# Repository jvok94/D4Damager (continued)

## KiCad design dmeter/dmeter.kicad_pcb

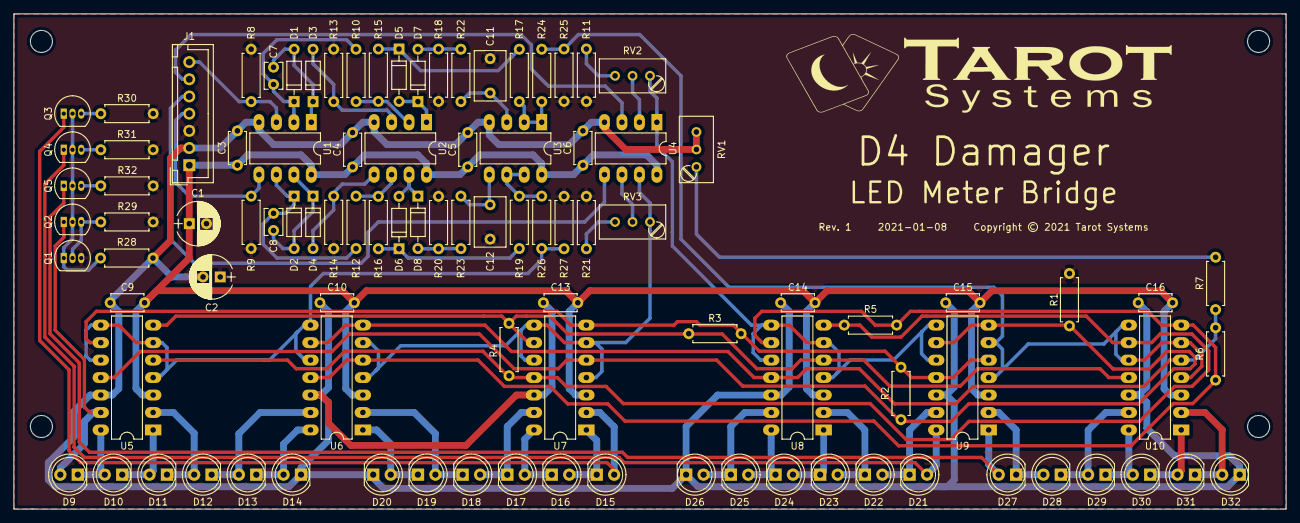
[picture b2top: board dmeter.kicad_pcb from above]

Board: 2 copper layers, 185.0 x 72.0 mm, 104 parts (0 on the bottom side), 69 nets.

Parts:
C1, C2: 100u 25V; CP_Radial_D6.3mm_P2.50mm
C3, C4, C5, C6, C9, C10, C13, C14, C15, C16: 100n; C_Disc_D4.7mm_W2.5mm_P5.00mm
C7, C8: 33p; C_Disc_D3.8mm_W2.6mm_P2.50mm
C11, C12: 560n; C_Rect_L7.2mm_W4.5mm_P5.00mm_FKS2_FKP2_MKS2_MKP2
D1, D2, D3, D4, D5, D6, D7, D8: 1N4148; D_DO-35_SOD27_P7.62mm_Horizontal
D9, D10, D11, D12, D15, D16, D17, D18, D19, D20, D21, D22, D23, D24, D25, D26, D27, D28, D29, D30: GREEN; LED_D5.0mm
D13, D31: YELLOW; LED_D5.0mm
D14, D32: RED; LED_D5.0mm
G1: LOGO; tarot_logo_fsilk_60mm
H1, H2, H3, H4: M3; MountingHole_3.2mm_M3
J1: INPUT; JST_XH_B07B-XH-A_07x2.50mm_Straight
Q1, Q2, Q3, Q4, Q5: BC556; TO-92_Inline_Narrow_Oval
R1, R2: 1k; R_Axial_DIN0207_L6.3mm_D2.5mm_P7.62mm_Horizontal_FabText
R3: 2k; R_Axial_DIN0207_L6.3mm_D2.5mm_P7.62mm_Horizontal_FabText
R4: 3k9; R_Axial_DIN0207_L6.3mm_D2.5mm_P7.62mm_Horizontal_FabText
R5: 8k2; R_Axial_DIN0207_L6.3mm_D2.5mm_P7.62mm_Horizontal_FabText
R6: 16k; R_Axial_DIN0207_L6.3mm_D2.5mm_P7.62mm_Horizontal_FabText
R7: 240k; R_Axial_DIN0207_L6.3mm_D2.5mm_P7.62mm_Horizontal_FabText
R8, R9, R10, R12, R13, R14, R15, R16, R17, R19, R24, R25, R27: 10k; R_Axial_DIN0207_L6.3mm_D2.5mm_P7.62mm_Horizontal_FabText
R11, R21: 390; R_Axial_DIN0207_L6.3mm_D2.5mm_P7.62mm_Horizontal_FabText
R18, R20: 1M; R_Axial_DIN0207_L6.3mm_D2.5mm_P7.62mm_Horizontal_FabText
R22, R23, R28: 5k6; R_Axial_DIN0207_L6.3mm_D2.5mm_P7.62mm_Horizontal_FabText
R26: 30k; R_Axial_DIN0207_L6.3mm_D2.5mm_P7.62mm_Horizontal_FabText
R29, R30, R31, R32: 100; R_Axial_DIN0207_L6.3mm_D2.5mm_P7.62mm_Horizontal_FabText
RV1, RV2, RV3: 10k; Potentiometer_Trimmer_Bourns_3296W_FabText
U1, U2, U3, U4: TL072; DIP-8_W7.62mm_LongPads
U5, U6, U7, U8, U9, U10: LM339; DIP-14_W7.62mm_LongPads

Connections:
+15V: C1.1, C3.1, C4.1, C5.1, C6.1, C9.1, C10.1, C13.1, C14.1, C15.1, C16.1, J1.1, U1.8 (V+), U2.8 (V+), U3.8 (V+), U4.8 (V+), U5.3 (V+), U6.3 (V+), U7.3 (V+), U8.3 (V+), U9.3 (V+), U10.3 (V+)
-15V: C2.2, C3.2, C4.2, C5.2, C6.2, C9.2, C10.2, C13.2, C14.2, C15.2, C16.2, D14.1 (K), D20.1 (K), D26.1 (K), D32.1 (K), J1.2, R28.2, RV1.2, RV1.3, U1.4 (V-), U2.4 (V-), U3.4 (V-), U4.4 (V-), U5.12 (V-), U6.12 (V-), U7.12 (V-), U8.12 (V-), U9.12 (V-), U10.12 (V-)
/VU0: R6.2, R7.1, U6.7 (+), U6.9 (+), U8.11 (+), U10.5 (+)
/VU6: R5.2, R6.1, U6.5 (+), U6.11 (+), U8.9 (+), U10.7 (+)
/VU12: R4.2, R5.1, U5.5 (+), U7.11 (+), U8.7 (+), U10.9 (+)
/VU18: R3.2, R4.1, U5.7 (+), U7.9 (+), U8.5 (+), U10.11 (+)
/VU24: R2.2, R3.1, U5.9 (+), U7.7 (+), U9.5 (+), U9.11 (+)
/VU30: R1.2, R2.1, U5.11 (+), U7.5 (+), U9.7 (+), U9.9 (+)
GND: C1.2, C2.1, C11.2, C12.2, J1.3, Q1.3 (E), R1.1, R8.2, R9.2, R11.2, R13.2, R14.2, R18.2, R20.2, R21.2, R25.2, R27.2, R29.1, R30.1, R31.1, R32.1
unnamed: C7.1, D1.1 (K), R10.2, U1.2 (-)
unnamed: C7.2, D1.2 (A), D3.1 (K), U1.1
unnamed: C8.1, D2.1 (K), R12.2, U1.6 (-)
unnamed: C8.2, D2.2 (A), D4.1 (K), U1.7
unnamed: C11.1, R22.1, U3.3 (+)
unnamed: C12.1, R23.1, U3.5 (+)
unnamed: D3.2 (A), R13.1, U2.3 (+)
unnamed: D4.2 (A), R14.1, U2.5 (+)
unnamed: D5.1 (K), R15.1, R17.2
unnamed: D5.2 (A), D7.1 (K), U2.1
unnamed: D6.1 (K), R16.1, R19.2
unnamed: D6.2 (A), D8.1 (K), U2.7
unnamed: D7.2 (A), R18.1, R22.2
unnamed: D8.2 (A), R20.1, R23.2
unnamed: D9.2 (A), Q2.1 (C), U5.13
unnamed: D10.1 (K), D11.2 (A), U5.1
unnamed: D9.1 (K), D10.2 (A), U5.14
unnamed: D11.1 (K), D12.2 (A), U5.2
unnamed: D12.1 (K), D13.2 (A), U6.13
unnamed: D13.1 (K), D14.2 (A), U6.14
unnamed: D15.1 (K), D16.2 (A), U7.1
unnamed: D15.2 (A), Q3.1 (C), U7.2
unnamed: D16.1 (K), D17.2 (A), U7.14
unnamed: D17.1 (K), D18.2 (A), U7.13
unnamed: D18.1 (K), D19.2 (A), U6.2
unnamed: D19.1 (K), D20.2 (A), U6.1
unnamed: D21.1 (K), D22.2 (A), U9.13
unnamed: D21.2 (A), Q4.1 (C), U9.14
unnamed: D22.1 (K), D23.2 (A), U8.2
unnamed: D23.1 (K), D24.2 (A), U8.1
unnamed: D24.1 (K), D25.2 (A), U8.14
unnamed: D25.1 (K), D26.2 (A), U8.13
unnamed: D27.1 (K), D28.2 (A), U9.2
unnamed: D27.2 (A), Q5.1 (C), U9.1
unnamed: D28.1 (K), D29.2 (A), U10.13
unnamed: D29.1 (K), D30.2 (A), U10.14
unnamed: D30.1 (K), D31.2 (A), U10.1
unnamed: D31.1 (K), D32.2 (A), U10.2
unnamed: J1.4, R9.1, U1.5 (+)
unnamed: J1.5, U4.5 (+)
unnamed: J1.6, U4.3 (+)
unnamed: J1.7, R8.1, U1.3 (+)
unnamed: Q1.1 (C), Q2.2 (B), Q3.2 (B), Q4.2 (B), Q5.2 (B), R28.1
unnamed: Q1.2 (B), Q2.3 (E), R29.2
unnamed: Q3.3 (E), R30.2
unnamed: Q4.3 (E), R31.2
unnamed: Q5.3 (E), R32.2
unnamed: R7.2, RV1.1
unnamed: R10.1, R15.2, U2.2 (-)
unnamed: R11.1, RV2.3
unnamed: R12.1, R16.2, U2.6 (-)
unnamed: R17.1, R24.1, U3.1, U3.2 (-)
unnamed: R19.1, R26.1, U3.6 (-), U3.7
unnamed: R21.1, RV3.3
unnamed: R24.2, R25.1, U9.4 (-), U9.6 (-), U10.4 (-), U10.6 (-), U10.8 (-), U10.10 (-)
unnamed: R26.2, R27.1, U5.4 (-), U5.6 (-), U5.8 (-), U5.10 (-), U6.8 (-), U6.10 (-)
unnamed: RV2.1, U4.1, U8.4 (-), U8.6 (-), U8.8 (-), U8.10 (-), U9.8 (-), U9.10 (-)
unnamed: RV2.2, U4.2 (-)
unnamed: RV3.1, U4.7, U6.4 (-), U6.6 (-), U7.4 (-), U7.6 (-), U7.8 (-), U7.10 (-)
unnamed: RV3.2, U4.6 (-)

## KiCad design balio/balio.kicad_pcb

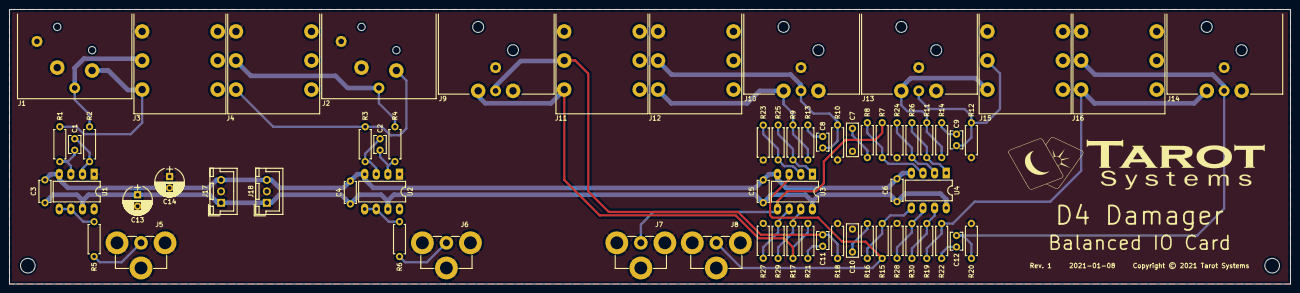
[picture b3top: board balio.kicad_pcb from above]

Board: 2 copper layers, 280.0 x 60.0 mm, 69 parts (0 on the bottom side), 41 nets.

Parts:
C1, C2, C8, C9, C11, C12: 560p; C_Disc_D3.8mm_W2.6mm_P2.50mm
C3, C4, C5, C6: 100n; C_Disc_D4.7mm_W2.5mm_P5.00mm
C7, C10: *; C_Rect_L7.2mm_W2.5mm_P5.00mm_FKS2_FKP2_MKS2_MKP2
C13, C14: 100u 25V; CP_Radial_D6.3mm_P2.50mm
G1: LOGO; tarot_logo_fsilk_60mm
H1, H2: M3; MountingHole_3.2mm_M3
J1: IN1; NC3FAAH2
J2: IN2; NC3FAAH2
J3: IN1; CL12345
J4: IN2; CL12345
J5: OUT1; NYS354
J6: OUT2; NYS354
J7: IN3; NYS354
J8: IN4; NYS354
J9: OUT3; NC3MAAH
J10: OUT4; NC3MAAH
J11: OUT3; CL12345
J12: OUT4; CL12345
J13: MON3; NC3MAAH
J14: MON4; NC3MAAH
J15: MON3; CL12345
J16: MON4; CL12345
J17, J18: POWER; JST_XH_B03B-XH-A_03x2.50mm_Straight
R1, R2, R3, R4, R23, R24, R25, R26, R27, R28, R29, R30: 2k2; R_Axial_DIN0207_L6.3mm_D2.5mm_P7.62mm_Horizontal_FabText
R5, R6, R9, R10, R11, R12, R13, R14, R17, R18, R19, R20, R21, R22: 220; R_Axial_DIN0207_L6.3mm_D2.5mm_P7.62mm_Horizontal_FabText
R7, R8, R15, R16: *; R_Axial_DIN0207_L6.3mm_D2.5mm_P7.62mm_Horizontal_FabText
U1, U2: INA134; DIP-8_W7.62mm_LongPads
U3, U4: TL072; DIP-8_W7.62mm_LongPads

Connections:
+15V: C3.2, C4.2, C5.1, C6.1, C13.1, J17.1, J18.1, U1.7 (VDD), U2.7 (VDD), U3.8 (V+), U4.8 (V+)
-15V: C3.1, C4.1, C5.2, C6.2, C14.2, J17.3, J18.3, U1.4 (VSS), U2.4 (VSS), U3.4 (V-), U4.4 (V-)
GND: C7.2, C10.2, C13.2, C14.1, J1.1, J1.G, J2.1, J2.G, J3.S, J4.S, J5.2 (Ext), J6.2 (Ext), J7.2 (Ext), J8.2 (Ext), J9.1, J9.G, J10.1, J10.G, J11.S, J12.S, J13.1, J13.G, J14.1, J14.G, J15.S, J16.S, J17.2, J18.2, R10.2, R12.2, R18.2, R20.2, R23.1, R24.1, R27.1, R28.1, U1.1 (REF), U2.1 (REF)
unnamed: C1.1, R2.1, U1.2 (IN-)
unnamed: C1.2, R1.1, U1.3 (IN+)
unnamed: C2.1, R4.1, U2.2 (IN-)
unnamed: C2.2, R3.1, U2.3 (IN+)
unnamed: C7.1, R8.2
unnamed: C8.1, R13.1
unnamed: C8.2, J10.3, J12.R, R10.1
unnamed: C9.1, R14.1
unnamed: C9.2, J13.3, J15.R, R12.1
unnamed: C10.1, R16.2
unnamed: C11.1, R21.1
unnamed: C11.2, J9.3, J11.R, R18.1
unnamed: C12.1, R22.1
unnamed: C12.2, J14.3, J16.R, R20.1
unnamed: J1.2, J3.T, R1.2
unnamed: J1.3, J3.R, R2.2
unnamed: J2.2, J4.T, R3.2
unnamed: J2.3, J4.R, R4.2
unnamed: J5.1 (In), R5.1
unnamed: J6.1 (In), R6.1
unnamed: J7.1 (In), R7.1, U3.5 (+)
unnamed: J8.1 (In), R15.1, U3.3 (+)
unnamed: J10.2, J12.T, R9.1, R13.2
unnamed: J9.2, J11.T, R17.1, R21.2
unnamed: J13.2, J15.T, R11.1, R14.2
unnamed: J14.2, J16.T, R19.1, R22.2
unnamed: R5.2, U1.5 (SENSE), U1.6 (OUT)
unnamed: R6.2, U2.5 (SENSE), U2.6 (OUT)
unnamed: R7.2, R8.1, U4.3 (+)
unnamed: R9.2, R25.1, U3.1
unnamed: R11.2, R26.1, U4.1
unnamed: R15.2, R16.1, U4.5 (+)
unnamed: R17.2, R29.1, U3.7
unnamed: R19.2, R30.1, U4.7
unnamed: R23.2, R25.2, U3.2 (-)
unnamed: R24.2, R26.2, U4.2 (-)
unnamed: R27.2, R29.2, U3.6 (-)
unnamed: R28.2, R30.2, U4.6 (-)

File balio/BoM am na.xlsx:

Reference | Quantity | Value | Footprint | Description | Manufacturer | Part number | Supplier | Order code | Price | Total | Notes
C1 C8 C9 C2 C11 C12 | 6 | 560p | Radial disc W4mm T2.6mm S2.5mm | 560pF 50V 5% C0G | Vishay | K561J15C0GF5TL2 | Farnell | 2860139 | 0.13500000000000001 | 0.81
C3 C4 C5 C6 | 4 | 100n | Radial disc W4mm T2.6mm S5mm | 100nF 50V 10% X7R | Vishay | K104K15X7RF53H5 | Farnell | 1141777 | 8.2299999999999998E-2 | 0.32919999999999999
C7 C10 | 2 | 4n7 | Radial box W7.2mm T2.5mm S5mm | 4.7nF 100V 10% film | Kemet | R82EC1470DQ50K | Farnell | 2763226 | 0.11 | 0.22
C13 C14 | 2 | 100u 25V | Radial can D6mm S2.5mm | 100uF 25V 20% 85C electrolytic | Kemet | ESK107M025AE3AA | Farnell | 2068981 | 8.0500000000000002E-2 | 0.161
J1 J2 | 2 |  | NC3FAAH2 | 3-pin XLR female PCB mount | Neutrik | NC3FAAH2 | Farnell | 1310023 | 0.93899999999999995 | 1.8779999999999999
J3 J4 J11 J12 J15 J16 | 6 |  | CL12345 | 6.35mm TRS PCB mount | Cliff | CL12345 | Farnell | 2766186 | 1.18 | 7.08
J5 J6 J7 J8 | 4 |  | NYS354 | NYS354 | Rean | NYS354 | Mouser | 568-NYS354 | 0.59 | 2.36
J9 J10 J13 J14 | 4 |  | NC3MAAH | 3-pin XLR male PCB mount | Neutrik | NC3MAAH | Farnell | 1310044 | 0.879 | 3.516
J17 J18 | 2 | POWER | B3B-XH-A | 1x3-pin 2.5mm pitch shrouded header | JST | B3B-XH-A (LF)(SN) | Farnell | 1516277 | 9.2499999999999999E-2 | 0.185
R1 R2 R3 R4 R24 R26 R23 R25 R27 R29 R28 R30 | 12 | 2k2 | Axial 6.8mm | 2.2k 0.6W 1% metal film | Multicomp | MCMF006FF2201A50 | Farnell | 2401762 | 2.8299999999999999E-2 | 0.33960000000000001
R5 R9 R13 R10 R11 R14 R12 R6 R17 R21 R18 R19 R22 R20 | 14 | 220 | Axial 6.8mm | 220R 0.6W 1% metal film | Multicomp | MCMF006FF2200A50 | Farnell | 2401736 | 2.8799999999999999E-2 | 0.4032
R7 R15 | 2 | 12k | Axial 6.8mm | 12k 0.6W 1% metal film | Multicomp | MCMF006FF1202A50 | Farnell | 2401783 | 2.8400000000000002E-2 | 5.6800000000000003E-2
R8 R16 | 2 | 3k9 | Axial 6.8mm | 3.9k 0.6W 1% metal film | Multicomp | MCMF006FF3901A50 | Farnell | 2401768 | 3.0200000000000001E-2 | 6.0400000000000002E-2
U1 U2 | 2 | INA134 | DIP-8 | 36V balanced audio receiver | Texas Instruments | INA134PA | Farnell | 3005742 | 2.9 | 5.8
U3 U4 | 2 | TL072 | DIP-8 | Dual 36V JFET input opamp | Texas Instruments | TL072ACP | Farnell | 3117783 | 0.90500000000000003 | 1.81
 |  |  |  |  |  |  |  |  | Total | 25.009199999999996

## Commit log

2021-07-11 First rev PCBs
2021-07-12 Change C25 to 100pF to reduce high frequency attenuation
2021-07-12 Change R24 to 10k, R26 to 30k to correct input/output meter reference levels
2021-07-14 Changed LPF, pre-emphasis component values in AM (NA and RoW) variants to correct bandwidth
2021-07-14 Changed Balanced IO card de-emphasis circuit in AM RoW variant to match pre-emphasis changes in previous commit
2021-07-14 Fixed some BoM formatting issues
2021-07-17 Fixed molex connector pin diameter
2021-07-17 Optimise pre-emphasis network values
2022-09-19 Upgrade amproc to Kicad 6
2022-09-19 Upgrade balio to Kicad 6
2022-09-19 Upgrade dmeter to Kicad 6
2022-09-19 Fix U8, U9 pinouts
2022-09-19 Change R10 to 430k to increase minimum release time
